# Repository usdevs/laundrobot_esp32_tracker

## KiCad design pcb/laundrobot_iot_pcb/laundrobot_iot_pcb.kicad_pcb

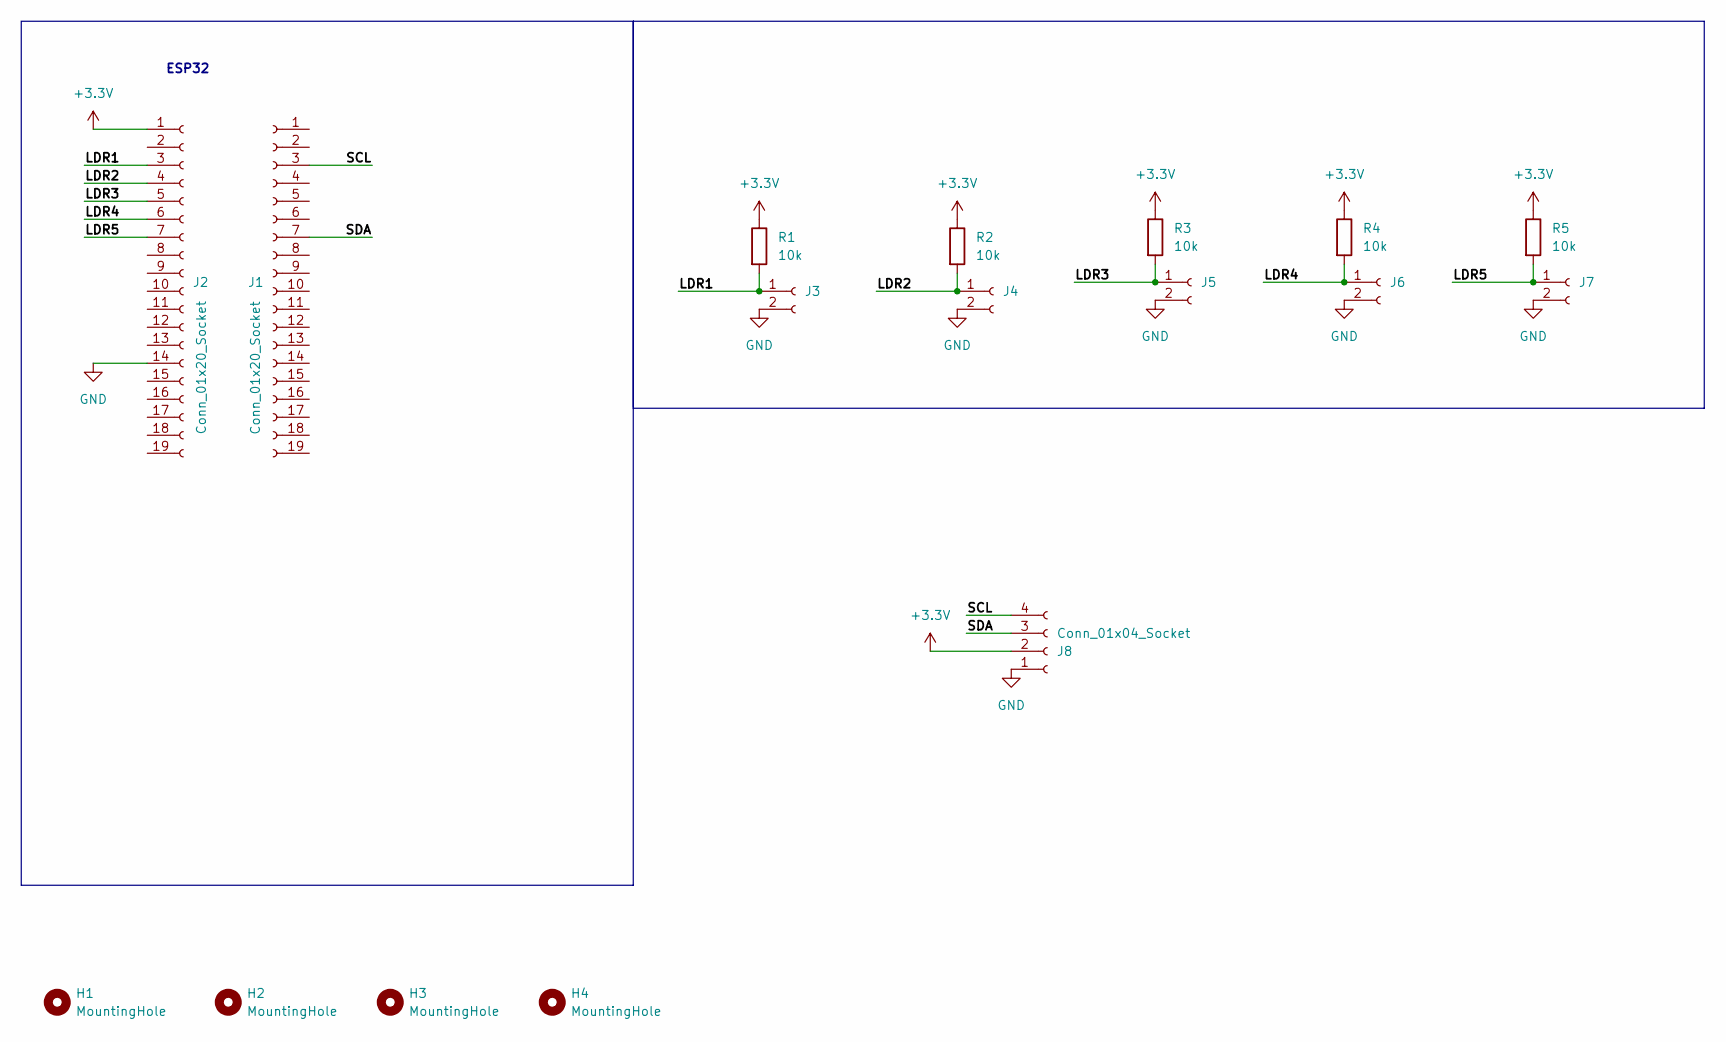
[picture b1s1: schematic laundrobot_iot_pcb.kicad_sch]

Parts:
H1, H2, H3, H4: MountingHole; MountingHole_3.2mm_M3_DIN965_Pad
J1, J2: Conn_01x20_Socket; PinSocket_1x19_P2.54mm_Vertical
J3, J4, J5, J6, J7: Conn_01x02_Socket; JST_XH_B2B-XH-AM_1x02_P2.50mm_Vertical
J8: Conn_01x04_Socket; PinSocket_1x04_P2.54mm_Vertical
R1, R2, R3, R4, R5: 10k; R_Axial_DIN0207_L6.3mm_D2.5mm_P10.16mm_Horizontal

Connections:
+3.3V: J2.1, J8.2, R1.1, R2.1, R3.1, R4.1, R5.1
/LDR1: J2.3, J3.1, R1.2
/LDR2: J2.4, J4.1, R2.2
/LDR3: J2.5, J5.1, R3.2
/LDR4: J2.6, J6.1, R4.2
/LDR5: J2.7, J7.1, R5.2
/SCL: J1.3, J8.4
/SDA: J1.7, J8.3
GND: J2.14, J3.2, J4.2, J5.2, J6.2, J7.2, J8.1

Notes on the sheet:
ESP32

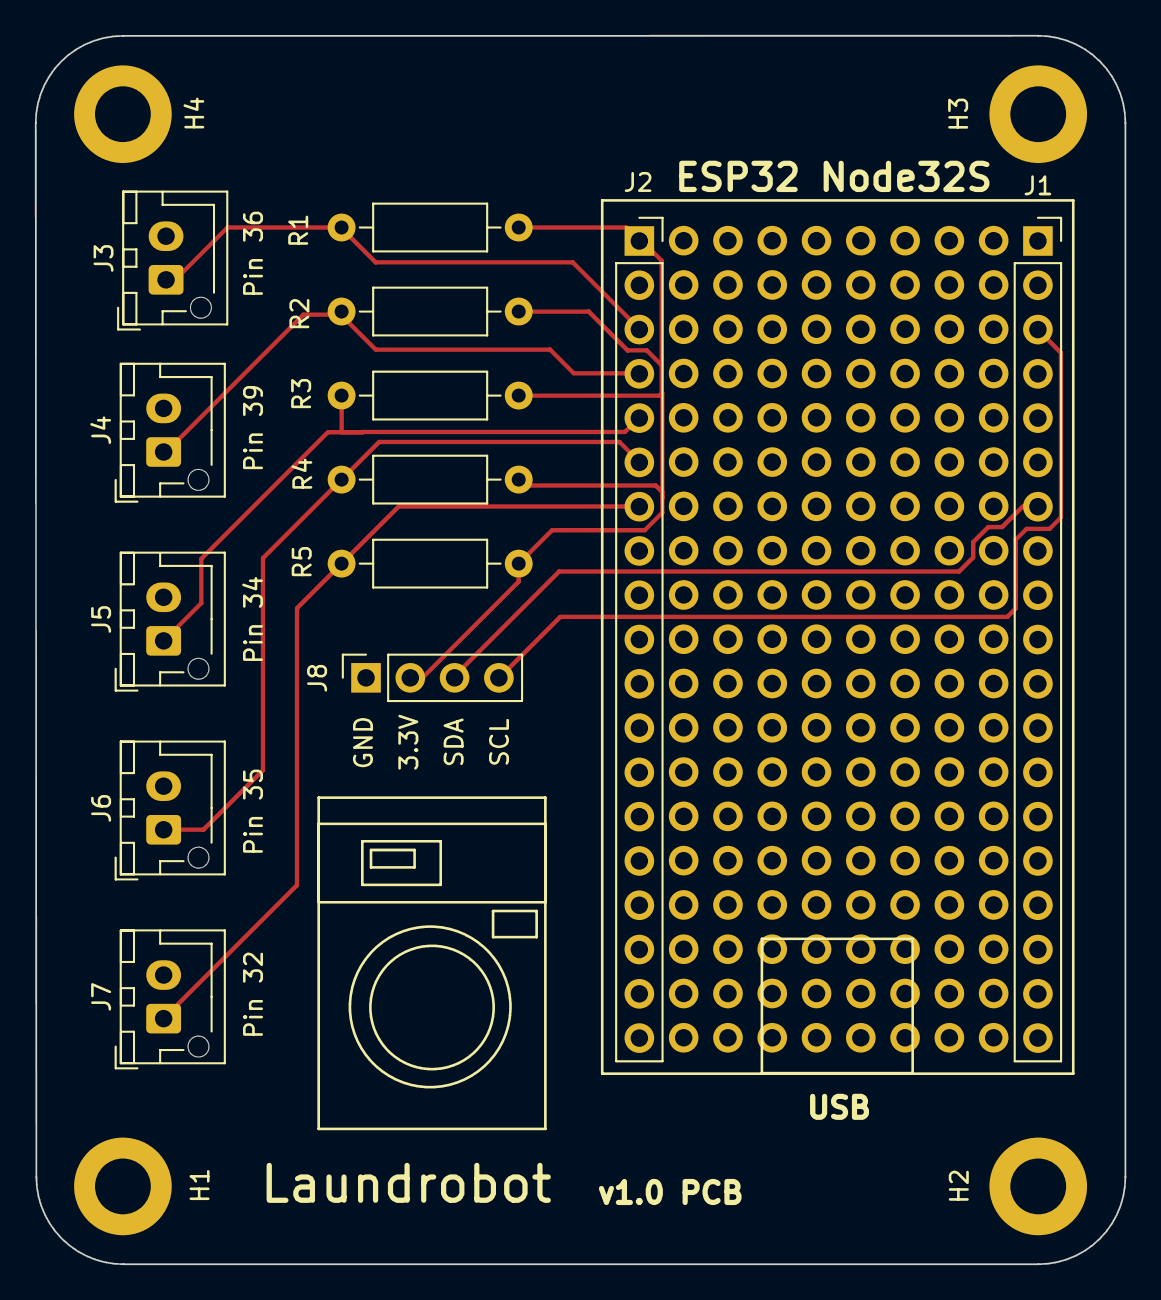
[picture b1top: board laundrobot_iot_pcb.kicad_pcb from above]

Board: 2 copper layers, 62.5 x 70.5 mm, 17 parts (0 on the bottom side), 9 nets.

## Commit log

2025-01-13 feat: firmware and pcb
2025-01-13 feat: fusion 360 casing
2025-01-29 Update lightsensor.ino
    updated with elm washers
2025-03-19 Update lightsensor.ino
    Trust-based cinnamon at Cinnamon
    as of 18 March 2025
